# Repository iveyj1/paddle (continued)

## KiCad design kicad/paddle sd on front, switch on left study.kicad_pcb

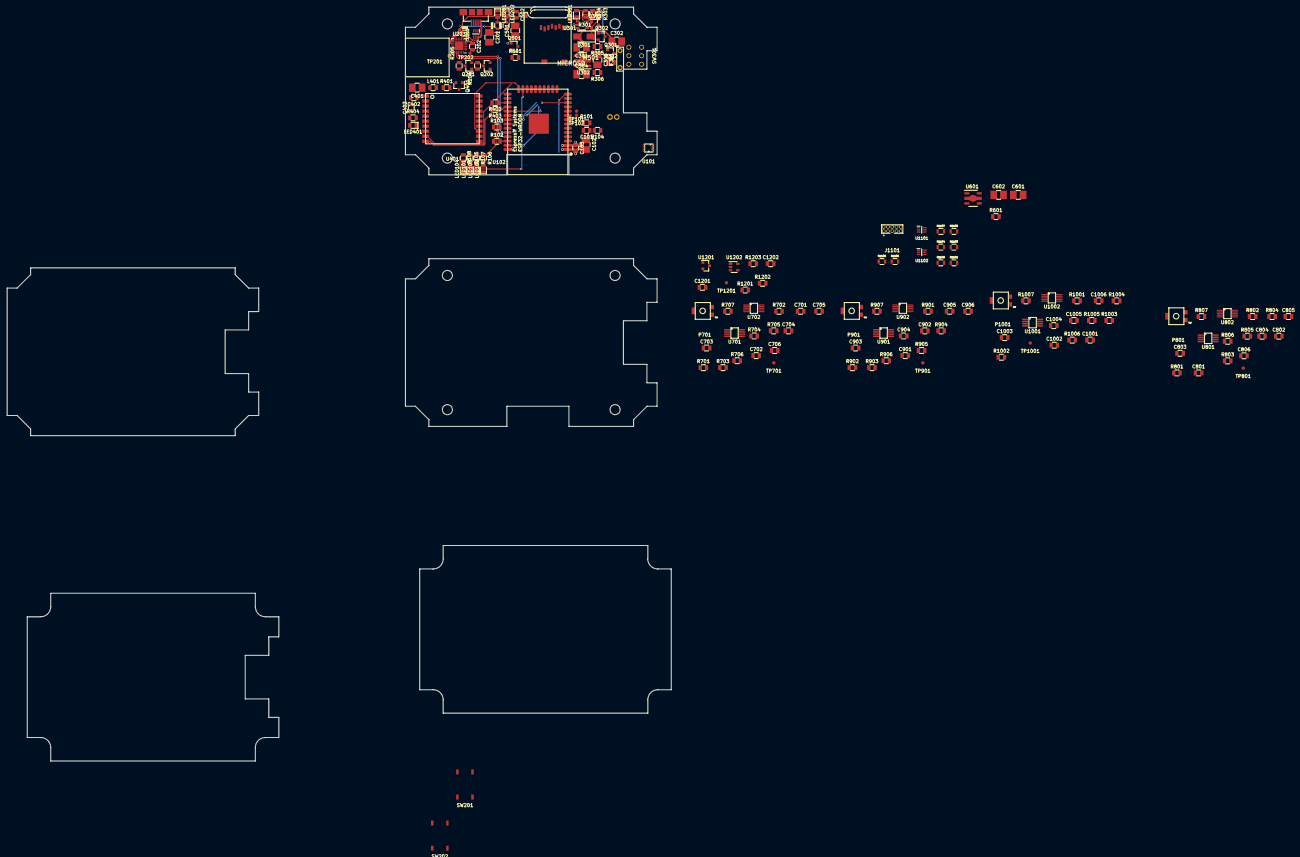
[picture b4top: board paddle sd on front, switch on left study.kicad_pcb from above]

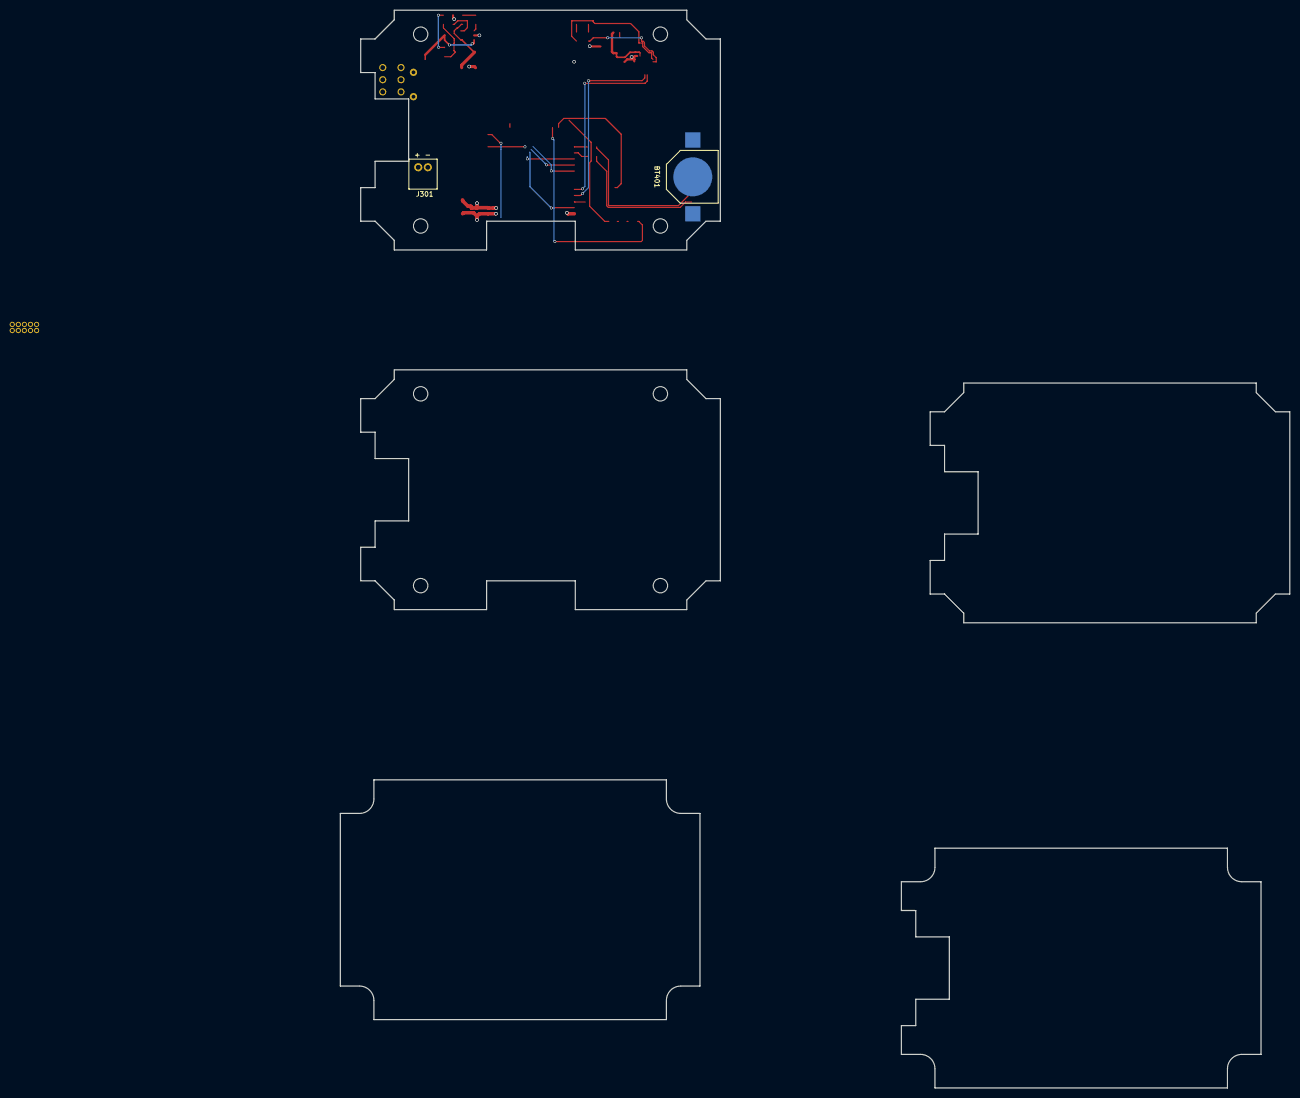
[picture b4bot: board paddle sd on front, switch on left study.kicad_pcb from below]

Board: 4 copper layers, 165 parts (2 on the bottom side), 115 nets.

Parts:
BT401: CR1025; CR1025_holder
C101: 1.0uF; SMD_0805
C102, C201, C301, C302, C303, C304, C401, C501, C601, C602: 10uF; SMD_1206
C103, C202, C502, C704, C804, C904, C1004, C1202: 0.1uF; SMD_0805
C402, C701, C702, C705, C801, C802, C805, C901, C902, C905, C1001, C1002, C1005: 0.01uF; SMD_0805
C403: 1uF; SMD_0805
C703, C803, C903, C1003: DNP 0.01uF; SMD_0805
C706, C806, C906, C1006: 0.22uF; SMD_0805
C1201: DNP 0.1uF; SMD_0805
D301: Schottky; D_SMA
F301: 1A Poly; radial-0.2-in-0.7mm-hole
J301: Battery; JST_battery_header_B2B-PH-K-S
J1101: CONN_02X05; header-0.050-10-pin-through-hole
L401: bead; SMD_0805
LED101, LED102, LED103, LED104, LED201, LED202, LED401: LED; SMD_D_0805
LED301: Charge; SMD_D_0805
M501: MICROSD
P701, P801, P901, P1001: 100k; TT_model_23_pot_smd_4mm
Q201, Q202: MMBT4401; SOT-23
Q301: DMG3414U; SOT-23
Q302, Q303, Q401, Q501: DMG3415U; SOT-23
R101, R104, R204, R205, R706, R806, R906, R1006, R1201, R1203: 10k; SMD_0805
R102, R103: 4.7k; SMD_0805
R105, R106, R107, R108, R402, R403, R404: 330; SMD_0805
R201: 1k; R_0805
R202, R203: 330; R_0805
R301: 1.0K; SMD_0805
R302, R303: 1Meg; SMD_0805
R304: 4.7K; SMD_0805
R305: 1.0Meg; SMD_0805
R306, R601: 100k; SMD_0805
R401, R501: 1MEG; SMD_0805
R701, R801, R901, R1001: 10k 0.1%; SMD_0805
R702, R802, R902, R1002: 20k 0.1%; SMD_0805
R703, R803, R903, R1003: 1.0M; SMD_0805
R704, R804, R904, R1004: 250; SMD_0805
R705, R805, R905, R1005, R1202: 0; SMD_0805
R707, R807, R907, R1007: DNP 100k; SMD_0805
R1101, R1102, R1103, R1104, R1105, R1106, R1107, R1108: 10k 0.1%; R_0805
SW201: RESET*; SW_TACTILE_PB_SMD_6MM
SW202: BOOTLOAD*; SW_TACTILE_PB_SMD_6MM
SW301: SW_DPDT_x2; dpdt_switch
TP101: IO26; tp_th_1mm
TP102: IO33; tp_th_1mm
TP201: RXD; tp_th_1mm
TP202: TXD; tp_th_1mm
TP701, TP801, TP901, TP1001, TP1201: AN1; tp_th_1mm
U101: BME280
U102: ESP32-WROOM
U201: USB_B_Socket; USB_micro_B_FCI_10104110
U202, U1101, U1102: SP3003-04; SMD_SC70-6
U203: CP2104; QFN-24-1EP_4x4mm_Pitch0.5mm
U301: MCP73831/2; SOT-23-5
U302, U601: NCP694-3.3; SOT89-5
U401: FGPMMOPA6H GPS; FGPMMOPA6H
U701, U801, U901, U1001: INA333; S-PDSO-G8
U702, U802, U902, U1002: ADS1115; VSSOP10-S-PDSO-G10
U1201: DNP TLVH431; SOT-23
U1202: OPA333; sot23-5

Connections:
+3.3VA: C602.1, C704.1, C706.1, C804.1, C806.1, C904.1, C906.1, C1004.1, C1006.1, C1202.1, J1101.1, P701.3, P801.3, P901.3, P1001.3, R1203.1, U601.5, U701.7, U702.8, U801.7, U802.1, U802.8, U901.7, U902.8, U1001.7, U1002.8, U1202.5
+3V3: C102.1, C103.1, C201.1, C202.1, C304.1, Q401.2, Q501.2, R101.1, R102.1, R103.1, R104.1, R201.2, R306.2, R501.1, U101.2, U101.6, U101.8, U102.2, U202.5, U203.5, U203.6, U203.7, U302.5, U1101.5, U1102.5
/1PPS: U102.24, U401.13
/+3.3VA_ENABLE: R601.2, U102.8, U601.3
/+V_UNREG_SW: C303.1, C601.1, Q302.3, SW301.2, U302.3, U302.4, U601.4
/ALERT0: R101.2, U102.6, U702.2, U802.2, U902.2, U1002.2
/BOOTLOAD*: Q201.3, U102.25
/ESP32_RESET*: C101.1, Q202.3, R104.2, U102.3
/GPS_EN*: Q401.1, R401.2, U102.26
/GPS_RXD: R403.1, U102.28
/GPS_TXD: R402.1, U102.27
/KEEPALIVE: Q301.1, R302.2, U102.11
/LEDB: R108.1, U102.23
/LEDG: R105.1, U102.13
/LEDR: R106.1, U102.16
/LEDY: R107.1, U102.14
/Power/+VBUS: C301.1, D301.A, Q303.1, R301.1, R305.2, U201.1, U202.6, U203.8, U301.4
/Power/V_BAT: C302.1, F301.1, Q303.3, U301.3
/Power/V_UNREG: D301.K, Q302.2, Q303.2, R303.2, SW301.1
/RXD: TP202.1, U102.35, U203.21
/SCK: R102.2, U101.4, U102.36, U702.10, U802.10, U902.10, U1002.1, U1002.10
/SD/CS: M501.2, U102.29
/SD/DATA_IN: M501.3, U102.37
/SD/DATA_OUT: M501.7, U102.31
/SD/SCLK: M501.5, U102.30
/SDA: R103.2, U101.3, U102.33, U702.9, U802.9, U902.1, U902.9, U1002.9
/SD_ENABLE*: Q501.1, R501.2, U102.12
/SHUTDOWN*: R306.1, SW301.5, U102.7
/TXD: TP201.1, U102.34, U203.20
/analog/AUX_IN_0: R706.2, R1101.1, U1101.6
/analog/AUX_IN_1: R806.2, R1102.1, U1101.4
/analog/AUX_IN_2: R906.2, R1103.1, U1101.3
/analog/AUX_IN_3: R1006.2, R1104.1, U1101.1
/analog/IN_0: R701.2, R1105.2, U1102.6
/analog/IN_1: R801.2, R1106.2, U1102.4
/analog/IN_2: R901.2, R1107.2, U1102.3
/analog/IN_3: R1001.2, R1108.2, U1102.1
/analog/VREF: R702.2, R802.2, R902.2, R1002.2, TP1201.1, U701.5, U702.7, U801.5, U802.7, U901.5, U902.7, U1001.5, U1002.7, U1202.1, U1202.4
GND: BT401.-, C101.2, C102.2, C103.2, C201.2, C202.2, C301.2, C302.2, C303.2, C304.2, C401.2, C402.2, C403.2, C501.2, C502.2, C601.2, C602.2, C701.2, C702.2, C704.2, C705.2, C706.2, C801.2, C802.2, C804.2, C805.2, C806.2, C901.2, C902.2, C904.2, C905.2, C906.2, C1001.2, C1002.2, C1004.2, C1005.2, C1006.2, C1201.2, C1202.2, J301.2, J1101.10, LED101.K, LED102.K, LED103.K, LED104.K, LED201.K, LED202.K, LED401.K, M501.6, M501.MT1, M501.MT2, P701.1, P801.1, P901.1, P1001.1, Q301.2, R302.1, R304.1, R305.1, R601.1, R705.1, R707.1, R805.1, R807.1, R905.1, R907.1, R1005.1, R1007.1, R1202.2, SW301.6, U101.1, U101.5, U101.7, U102.1, U102.15, U102.38, U102.39, U201.5, U201.6, U202.2, U203.2, U203.25, U301.2, U302.2, U401.3, U401.8, U401.12, U401.19, U601.2, U702.1, U702.3, U802.3, U902.3, U1002.3, U1101.2, U1102.2, U1201.3, U1202.2
unnamed: BT401.+, C403.1, U401.4
unnamed: C401.1, C402.1, L401.1, U401.1
unnamed: C501.1, C502.1, M501.4, Q501.3
unnamed: C701.1, C703.2, R701.1, U701.3
unnamed: C702.1, C703.1, R702.1, R703.1, U701.2
unnamed: C705.1, R706.1, R707.2, U702.4
unnamed: C801.1, C803.2, R801.1, U801.3
unnamed: C802.1, C803.1, R802.1, R803.1, U801.2
unnamed: C805.1, R806.1, R807.2, U802.4
unnamed: C901.1, C903.2, R901.1, U901.3
unnamed: C902.1, C903.1, R902.1, R903.1, U901.2
unnamed: C905.1, R906.1, R907.2, U902.4
unnamed: C1001.1, C1003.2, R1001.1, U1001.3
unnamed: C1002.1, C1003.1, R1002.1, R1003.1, U1001.2
unnamed: C1005.1, R1006.1, R1007.2, U1002.4
unnamed: C1201.1, R1201.1, R1203.2, U1201.2, U1202.3
unnamed: F301.2, J301.1
unnamed: J1101.2, R1105.1
unnamed: J1101.3, R1101.2
unnamed: J1101.4, R1106.1
unnamed: J1101.5, R1102.2
unnamed: J1101.6, R1107.1
unnamed: J1101.7, R1103.2
unnamed: J1101.8, R1108.1
unnamed: J1101.9, R1104.2
unnamed: L401.2, Q401.3
unnamed: LED101.A, R105.2
unnamed: LED102.A, R106.2
unnamed: LED103.A, R107.2
unnamed: LED104.A, R108.2
unnamed: LED201.A, R202.2
unnamed: LED202.A, R203.2
unnamed: LED301.A, R301.2
unnamed: LED301.K, U301.1
unnamed: LED401.A, R404.1
unnamed: P701.2, R703.2
unnamed: P801.2, R803.2
unnamed: P901.2, R903.2
unnamed: P1001.2, R1003.2
unnamed: Q201.1, R205.1
unnamed: Q201.2, R204.2, U203.23
unnamed: Q202.1, R204.1
unnamed: Q202.2, R205.2, U203.19
unnamed: Q301.3, Q302.1, R303.1
unnamed: R201.1, U203.9
unnamed: R202.1, U203.14
unnamed: R203.1, U203.13
unnamed: R304.2, U301.5
unnamed: R402.2, U401.9
unnamed: R403.2, U401.10
unnamed: R404.2, U401.5
unnamed: R704.1, U701.1
unnamed: R704.2, U701.8
unnamed: R705.2, U701.4
unnamed: R804.1, U801.1
unnamed: R804.2, U801.8
unnamed: R805.2, U801.4
unnamed: R904.1, U901.1
unnamed: R904.2, U901.8
unnamed: R905.2, U901.4
unnamed: R1004.1, U1001.1
unnamed: R1004.2, U1001.8
unnamed: R1005.2, U1001.4
unnamed: R1201.2, R1202.1, U1201.1
unnamed: TP101.1, U102.10
unnamed: TP102.1, U102.9
unnamed: TP701.1, U702.5
unnamed: TP801.1, U802.5
unnamed: TP901.1, U902.5
unnamed: TP1001.1, U1002.5
unnamed: U201.2, U202.3, U203.4
unnamed: U201.3, U202.4, U203.3
unnamed: U701.6, U702.6
unnamed: U801.6, U802.6
unnamed: U901.6, U902.6
unnamed: U1001.6, U1002.6

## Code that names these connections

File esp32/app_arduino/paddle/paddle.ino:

#include <Wire.h>
#include <HardwareSerial.h>
#include <FS.h>
#include "SD.h"
#include "SPI.h"
#include <WiFi.h>

#define EXPANDER_ADDR 0x38

// IO ports
#define KEEPALIVE 4
#define POWER_SW 35
#define BLINK 13
//#define cardselect 5

// Expander bits
#define LED0 0x00u
#define LED1 0x01u
#define LED2 0x02u
#define LED3 0x03u
#define VA_3_3_ENABLE 0x04u
#define GPS_ENABLE 0x05u
#define SD_ENABLE 0x06u
#define AN_REFSEL 0x07u

#define TCA9534_IN_PORT 0x00
#define TCA9534_OUT_PORT 0x01
#define TCA9534_POL_PORT 0x02
#define TCA9534_DIR_PORT 0x03

#define bmask(mask) (1 << (mask))
#define cardSelect 5

//WiFi globals
const char* ssid     = "Cold Comfort Farm";
const char* password = "widephoenix967";
WiFiServer server(80);


// Globals
HardwareSerial Serial1(2); // GPS serial port
File logfile;

//timer variables
hw_timer_t * timer = NULL;
volatile SemaphoreHandle_t timerSemaphore;
portMUX_TYPE timerMux = portMUX_INITIALIZER_UNLOCKED;
volatile uint32_t isrCounter = 0;
volatile uint32_t lastIsrAt = 0;
volatile int margin = 0;
volatile int overrun;
long int overrun_time;

int i = 0;
unsigned long int lastloop = 0;
unsigned long int temp;
int error;
unsigned long int loopcount = 0;

void processLooptime()
{
    // If Timer has fired
    if (xSemaphoreTake(timerSemaphore, 0) == pdTRUE)
    { // blown loop time
        overrun = true;
        overrun_time = millis();
        bsetExpander(LED0, HIGH);
        Serial.print("Looptime: ");
        Serial.println(micros() - lastloop);
    }
    margin = 0;

    while (xSemaphoreTake(timerSemaphore, 0) != pdTRUE)
    {
        margin++;
    }
    lastloop = micros();


#if 0
    uint32_t isrCount = 0, isrTime = 0;
    // Read the interrupt count and time
    portENTER_CRITICAL(&timerMux);
    isrCount = isrCounter;
    isrTime = lastIsrAt;
    portEXIT_CRITICAL(&timerMux);
#endif

    if(overrun && (millis() > overrun_time + 5000))
    {
        overrun = false;
        //bsetExpander(LED0, LOW);
    }

#if 0
    if((loopcount++ % 10000) == 0)
    {
        delay(10);
    }
#endif  
    
}

void setup() {
    Serial.begin(115200);
    pinMode(BLINK, OUTPUT);
    Wire.begin();
    setupPower();
    setupExpander();
    setupGPS();
    setupSD();
    openAcqFile();
    setupTimer();
    setupWifi();
    overrun = false;
    overrun_time = millis();
    lastloop = micros();
    xSemaphoreTake(timerSemaphore, 0);
    p("asdf: %i",5);
}


void loop()
{
    int c;
    while (Serial1.available())
    {
        char c = Serial1.read();
        if (c)
        {
            ;//Serial.print(c);
        }
    }
    processLooptime();

    processWifi();
    checkPowerSwitch();
}

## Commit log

2017-08-17 original pre-keepalive Atmel version of paddle acquisiton released summer 2016
    paddle_acq_on_power_on06_rel
2017-08-17 Fix tabs, add diagnostics for SD problem
2017-08-17 More diagnostics for SD
2017-08-17 keeplaive support and diagnostics for SD, released to James paddle_fix_sd_02_2017-06-19
2017-08-17 add samd package from adafruit
2017-08-18 Add esp32 demo code - works with ESP32 Thing
2017-08-18 First cut paddle for esp32 - compiles but no a/d
2017-08-18 timer implemented in paddle_esp
2017-08-20 Add sd functionality
2017-08-20 Improve printed messages
2017-08-20 Remove unused functionality
2017-08-20 Start over - split into multiple ino files
2017-08-20 Add html and js files for plotting
2017-09-04 Pared down gps demo to serial dump only
    Fixed sd card pinout notes in sd demo
    Added Adafruit ADS1115 libraries
    Fiddle with gain on a/d
    Add resolution analysis Smath doc
2017-09-22 Add samd/AT 8266 server example code and javascript plotting flotr2
2017-09-24 Start of asynchronous a/d
2017-09-24 Add kicad files to project
2017-09-25 Fix up led footprints
2017-09-26 Add threshold writes to enable alert pin on a/d conversion complete
2017-09-26 Add LEDs to schematic, add pullup to ALERT0, remove ALERT 1-3
2017-09-26 Add resistors to inputs, put inputs in hierarchical blocks start bridge unbalance fixes
2017-09-27 layout sample analog a/d section, add buttons, battery but not footprints
2017-09-28 Finalize board outline, holes, grid
2017-09-28 More placement studies, last commit before parts reduction
2017-09-29 Added second board -
    lost footprint changes
2017-09-30 Separate analog block in schematic, fix up board outline, allow for connector, delete bad zones
2017-10-02 fix up buttons, move SD to top, add battery holder, add reverse diodes to regs,
    change to spst switch and add header for switch
2017-10-02 interrupt driven a/d seems to work
2017-10-04 fix diodes - last before 24-bit
    add switches?
2017-10-06 Start switch to 24-bit a/d, smaller buttons, add io expansion, prelim route digital
2017-10-07 more layout of digital, LTC2440 test code started
2017-10-08 working basic ltc2440 demo except sign bit
2017-10-08 fix a/d sign logic
2017-10-09 Clean up ads2440 code - works
2017-10-09 Fix up ADS1115 adc test code for new directory structure, change gain to 4 - shootout
2017-10-12 LTC2440 test code merged with ADS1115, finished analog and reference schematic, added reference footprint,
2017-10-13 Fix up digital connections - not done
2017-10-14 Fix up names, digital signals, finish reference
2017-10-15 Verify sensor, USB, part of power, add QI charger rectifier
2017-10-18 Start fix up of analog inputs and input+/-/ref tracking, amp model
2017-10-24 Simulations of analog inputs to a/d
2017-10-24 remove log and raw files
2017-10-30 More circuit analysis, before simplifying inputs and power
2017-10-30 After changes to power and amp
2017-11-04 began changes to separate boards
2017-11-04 add paddle.lib which was filtered out by .gitignore
2017-11-05 Restructure directories - separate projects for each board,
    separate directory for analysis, datasheets
2017-11-06 Finish split projects, fix ERC, import outline to processor board
2017-11-13 Logic board standalone about done, changed to 0603 resistors and 0805 caps
2017-11-13 updated spreadsheet
2017-11-13 start processor layout - footprint fixes
2017-11-20 First cut layout power supply, fix netclasses, footprint for connector
2017-12-04 Processor board routed, conn_FCI_14 switched to no hole version, port expander package fixed
2017-12-04 Fixed components under screws, silkscreen, exported gerbers
2017-12-09 Finished routing, DRC ok, moved origin to top left,
2017-12-09 processor RC1
2017-12-09 processor RC2
2017-12-10 checkpoint
2017-12-10 RC3 Fix vias too close to edge
2017-12-11 Switch to nightly Windows build
2017-12-11 Cleanup files from version switch
2017-12-11 Fix updated connector footprint
2017-12-13 Processor release 2017-12-13 sent to Gold Phoenix
2018-01-14 Update analog board to kicad v4
2018-01-14 Add datasheets
2018-01-14 BOM for previous release
2018-01-14 Updated demos for processor board (from breadboard version), cleanup
2018-01-14 Updated mfg files for previous release
2018-01-14 Add new app files, cleanup, add todo
2018-01-14 Cleanup mfg files, rearrange kicad directories, cleanup analog
2018-01-16 App with SD, power, expander working, GPS enabled
2018-01-16 Timers working, first cut at server, fixed errno error (conflict with function name)
2018-01-16 Basic LED on/off server works
2018-01-22 changed test code for i2c - using stickbreaker's I2C mods to ESP32 libraries
2018-01-24 In Arduino ESP32 code, wifi, looptime, SD, GPS, expander, all working, fixed tabs, added Wire examples, reorganized main loop
2018-02-21 Tests of arduino app
2018-02-21 wifi sniffer instructions
2018-02-21 initial idf app - SD works
2018-02-24 Tests with IDF app
2018-02-24 directory reorg
2018-03-01 created ESP-IDF main app, tasks, power, SD, GPS, expander working
2018-03-01 put old stuff in old/ directory
2018-03-01 add trash can to .gitignore
2018-03-04 GPS NMEA capture working
    Acq timer callback demo
    Power keepalive and SD functionality working
    SD Open next file function working
    added script to dump to flash on panic - not tested
2018-03-05 Simplify reference, fix connector pinout
2018-03-08 Add ADS1220 A/D
2018-03-11 Switch analog to ADS1220 a/d converter
2018-03-11 Split analog SPI to be separate from SD pins, USB bus powered, added caps, updated todo, more
2018-03-12 processor laid out, todo complete, connector for wireless charge
2018-03-12 Rearrange datasheets
2018-03-12 Analog board outline, holes, most footprints, schematic complete
2018-03-13 Fix FCI connector refs, footprints, all packages for analog, starting parts placement
2018-03-14 separate opamps for - input
2018-03-18 Sch: Added bypass caps opamps
    Layout: placement and traces for 1 a/d channel ok, connector in right location and pinout (mirror image of processor)
2018-03-19 analog routed DRC passes
2018-03-19 add bulk caps to analog
2018-03-28 Analog board and second rev processor board as sent to Goldphoenix
2018-03-28 Added ADS1220 A/D reading task, works with hardware, patched insufficient stack problems
2018-03-30 Fix behavior with no SD card installed, prints single ad output plus gps to SD and console
2018-03-30 Reorganize acquisition, SD, main logic, allow start/stop acquisition, opening new acq file
2018-04-08 Fix power button logic, fix GPS startup,
2018-04-09 Fix startup sequence for power
2018-04-09 remove esphttpd-freertos inadvertently added
2018-04-12 App, Fixed CS, works with one a/d board, all three a/d
2018-04-14 App working with 4 a/d, diff mode, vdd reference, gain 4
2018-04-14 AD working 20 ms sample time
2018-04-15 app added httpd, works for directory and single chunk file, fails for multichunk
2018-04-16 app server works with directories and files
2018-04-17 deleted: app/components/libesphttpd Delete libesphttpd
2018-04-17 re-added libesphttpd
2018-04-21 Web server, sd upload, long filenames, basically working
2018-04-21 Initial time of day, tweak routes, separate html and data dirs, still not working correctly
2018-04-22 App - basic browsing, test code for file tiime/size, js changes, upload + backup fn works,
2018-04-23 Displaying times and sizes in dir
2018-05-03 GPS and NMEA checksum, clock setting, a/d all work
2018-05-07 Add stack checks and report task status at shutdown
2018-05-07 Delay power off to let acq finish writing to SD 50->500 ms
2018-05-07 Make dir entry HTML point .csv files at /html/plot.html and add query for URL
2018-05-07 Move acq directory to /sdcard/data
2018-05-07 Enable trace, run time stats, stats fomatting function, singleapp coredump - needed for stack output below
2018-05-07 Report looptime in AD before looptime fix
2018-05-07 HTML/js for plotting CSV - works
2018-05-16 Broken - semaphore timeouts for no reason
2018-05-18 Fixed assert and watchdog issues, code still commented out
2018-05-19 File writes broken, fixed semaphore give in sd, Power off waits for acq file closedir, Flashdump com 4, Fixed semicolons in httpdfatfs (?)
    default message level verbose
2018-05-19 negative size file write fixed in sd.c:108, file writes ok on start, stop, power. Acq timing not correct
2018-05-19 Timing improved, removed ESP_LOGI from AD, added looptime monitoring, still erratic after start of acquisition
2018-05-19 Fixed timing at start of acq, now resets previous wake time after acq file opened (takes 250 ms)
2018-05-21 freezes, etc. in fwrite fixed?
2018-05-21 exceeds loop time esp when httpd running. Get rid of test code, switch processor affinity, indicator lights on file wright, file opened, sd mounted, modded libesphttpd to make server task affinity co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
2018-05-25 Start fixing up html/js, plot works with test case, can invoke test case with .../html/plot.html?url=dataa000.csv
2018-05-26 Added /dir/?dirurl=/foo/bar target to server that returns json with directory entries
2018-05-29 Directory, plot work on mobile. Reverted upload but doesn't work
2018-06-03 keepalive disabled, add download button, move most console messages to LOGD,
    root url goes to html/dir.html, reboot on panic
    Switch led 2 to be on when SD unmounted,
2018-06-03 Reduced stack size for acqwrite task, sdkconfig entries for updated ESP libraries - esphttpd task no longer bound to processor 0 due to change in libesphttpd
2018-06-03 updated libesphttpd
2018-06-14 As built changes: vbat sense, R207 100k, remove diode keepalive
2018-06-14 modified: app/main/ad.c modified: app/main/ad.h modified: app/main/paddle.c modified: app/main/power.c modified: app/main/power.h modified: app/main/sd.c modified: app/sdkconfig modified: app/sdkconf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
    Added diagnostics for SD files, power light, close file on low bat voltage
2018-06-18 Added partitions file to support ota, set sdkconfig to assume 4M memory
2018-06-18 added todo.txt
2018-06-18 fix low battery voltage shutdown
2018-06-24 OTA works
    OTA works
    start over with httpd_paddle from libesphttpd example from chmorgan,
    update libesphttpd
    improve log messages
    Reduce stack size for tasks
    Add heap size log messages - appears to be minimal leaks
2018-06-24 fixes for upload html
    console 115200, upload html works - fixed parmeter for cgiUploadSdFile
    in httpd_paddle.c, heap poisoning light,
2018-07-23 Add makefile sh to build without zlib/gzip
2018-07-26 add oscar.ods, eclipse debug instructions,
